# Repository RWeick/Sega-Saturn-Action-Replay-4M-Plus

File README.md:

# Sega-Saturn-Action-Replay-4M-Plus
The Kicad files, rom dump, and PAL JEDEC of the 16V8 for the Sega Saturn Action Replay 4M Plus

PCB Thickness: 1.6 mm

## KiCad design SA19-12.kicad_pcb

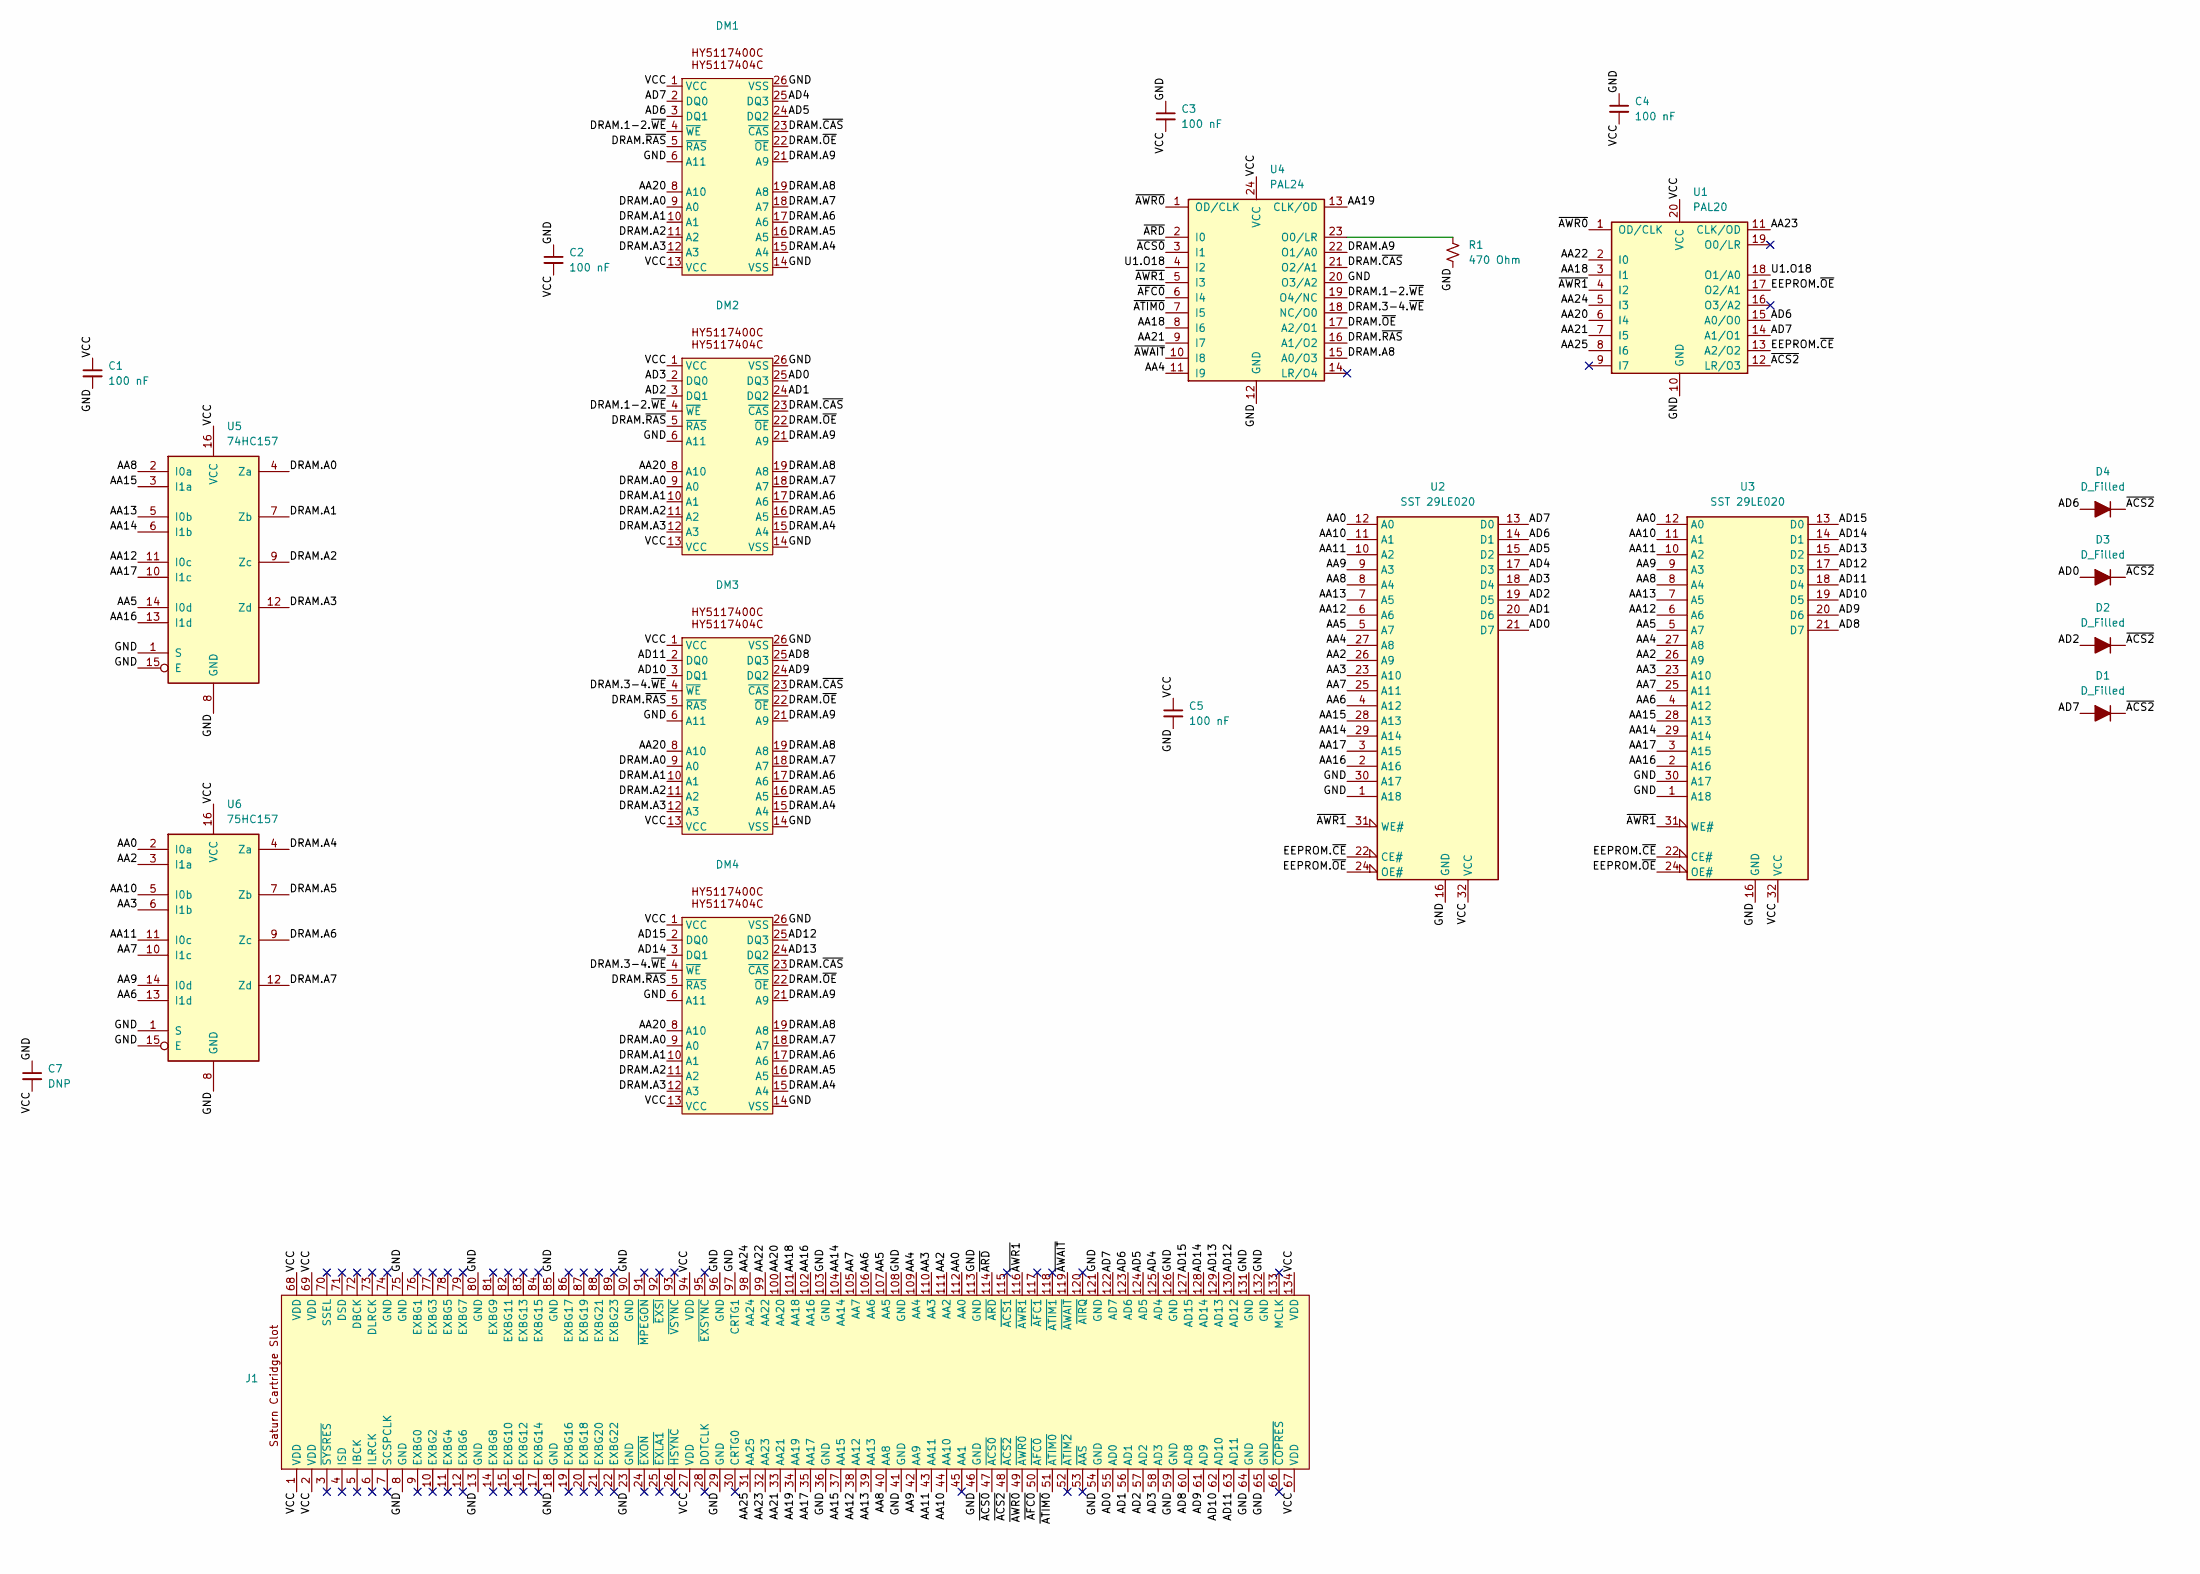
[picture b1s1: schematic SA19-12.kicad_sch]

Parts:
C1, C2, C3, C4, C5: 100 nF; SMD
C7: DNP; SMD
D1, D2, D3, D4: D_Filled; Diode
DM1, DM2, DM3, DM4: DRAM
J1: Edge Connecto5
R1: 470 Ohm; SMD
U1: PAL20; DIP-20_W7.62mm
U2, U3: SST 29LE020; PLCC-32
U4: PAL24; DIP-24_W7.62mm
U5: 74HC157; DIP-16_W7.62mm
U6: 75HC157; DIP-16_W7.62mm

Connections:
/AA0: J1.112 (AA0), U2.12 (A0), U3.12 (A0), U6.2 (I0a)
/AA2: J1.111 (AA2), U2.26 (A9), U3.26 (A9), U6.3 (I1a)
/AA3: J1.110 (AA3), U2.23 (A10), U3.23 (A10), U6.6 (I1b)
/AA4: J1.109 (AA4), U2.27 (A8), U3.27 (A8), U4.11 (I9)
/AA5: J1.107 (AA5), U2.5 (A7), U3.5 (A7), U5.14 (I0d)
/AA6: J1.106 (AA6), U2.4 (A12), U3.4 (A12), U6.13 (I1d)
/AA7: J1.105 (AA7), U2.25 (A11), U3.25 (A11), U6.10 (I1c)
/AA8: J1.40 (AA8), U2.8 (A4), U3.8 (A4), U5.2 (I0a)
/AA9: J1.42 (AA9), U2.9 (A3), U3.9 (A3), U6.14 (I0d)
/AA10: J1.44 (AA10), U2.11 (A1), U3.11 (A1), U6.5 (I0b)
/AA11: J1.43 (AA11), U2.10 (A2), U3.10 (A2), U6.11 (I0c)
/AA12: J1.38 (AA12), U2.6 (A6), U3.6 (A6), U5.11 (I0c)
/AA13: J1.39 (AA13), U2.7 (A5), U3.7 (A5), U5.5 (I0b)
/AA14: J1.104 (AA14), U2.29 (A14), U3.29 (A14), U5.6 (I1b)
/AA15: J1.37 (AA15), U2.28 (A13), U3.28 (A13), U5.3 (I1a)
/AA16: J1.102 (AA16), U2.2 (A16), U3.2 (A16), U5.13 (I1d)
/AA17: J1.35 (AA17), U2.3 (A15), U3.3 (A15), U5.10 (I1c)
/AA18: J1.101 (AA18), U1.3 (I1), U4.8 (I6)
/AA19: J1.34 (AA19), U4.13 (CLK/OD)
/AA20: DM1.8 (A10), DM2.8 (A10), DM3.8 (A10), DM4.8 (A10), J1.100 (AA20), U1.6 (I4)
/AA21: J1.33 (AA21), U1.7 (I5), U4.9 (I7)
/AA22: J1.99 (AA22), U1.2 (I0)
/AA23: J1.32 (AA23), U1.11 (CLK/OD)
/AA24: J1.98 (AA24), U1.5 (I3)
/AA25: J1.31 (AA25), U1.8 (I6)
/AD0: D3.2 (A), DM2.25 (DQ3), J1.55 (AD0), U2.21 (D7)
/AD1: DM2.24 (DQ2), J1.56 (AD1), U2.20 (D6)
/AD2: D2.2 (A), DM2.3 (DQ1), J1.57 (AD2), U2.19 (D5)
/AD3: DM2.2 (DQ0), J1.58 (AD3), U2.18 (D4)
/AD4: DM1.25 (DQ3), J1.125 (AD4), U2.17 (D3)
/AD5: DM1.24 (DQ2), J1.124 (AD5), U2.15 (D2)
/AD6: D4.2 (A), DM1.3 (DQ1), J1.123 (AD6), U1.15 (A0/O0), U2.14 (D1)
/AD7: D1.2 (A), DM1.2 (DQ0), J1.122 (AD7), U1.14 (A1/O1), U2.13 (D0)
/AD8: DM3.25 (DQ3), J1.60 (AD8), U3.21 (D7)
/AD9: DM3.24 (DQ2), J1.61 (AD9), U3.20 (D6)
/AD10: DM3.3 (DQ1), J1.62 (AD10), U3.19 (D5)
/AD11: DM3.2 (DQ0), J1.63 (AD11), U3.18 (D4)
/AD12: DM4.25 (DQ3), J1.130 (AD12), U3.17 (D3)
/AD13: DM4.24 (DQ2), J1.129 (AD13), U3.15 (D2)
/AD14: DM4.3 (DQ1), J1.128 (AD14), U3.14 (D1)
/AD15: DM4.2 (DQ0), J1.127 (AD15), U3.13 (D0)
/DRAM.1-2.~WE: DM1.4 (~WE), DM2.4 (~WE), U4.19 (O4/NC)
/DRAM.3-4.~WE: DM3.4 (~WE), DM4.4 (~WE), U4.18 (NC/O0)
/DRAM.A0: DM1.9 (A0), DM2.9 (A0), DM3.9 (A0), DM4.9 (A0), U5.4 (Za)
/DRAM.A1: DM1.10 (A1), DM2.10 (A1), DM3.10 (A1), DM4.10 (A1), U5.7 (Zb)
/DRAM.A2: DM1.11 (A2), DM2.11 (A2), DM3.11 (A2), DM4.11 (A2), U5.9 (Zc)
/DRAM.A3: DM1.12 (A3), DM2.12 (A3), DM3.12 (A3), DM4.12 (A3), U5.12 (Zd)
/DRAM.A4: DM1.15 (A4), DM2.15 (A4), DM3.15 (A4), DM4.15 (A4), U6.4 (Za)
/DRAM.A5: DM1.16 (A5), DM2.16 (A5), DM3.16 (A5), DM4.16 (A5), U6.7 (Zb)
/DRAM.A6: DM1.17 (A6), DM2.17 (A6), DM3.17 (A6), DM4.17 (A6), U6.9 (Zc)
/DRAM.A7: DM1.18 (A7), DM2.18 (A7), DM3.18 (A7), DM4.18 (A7), U6.12 (Zd)
/DRAM.A8: DM1.19 (A8), DM2.19 (A8), DM3.19 (A8), DM4.19 (A8), U4.15 (A0/O3)
/DRAM.A9: DM1.21 (A9), DM2.21 (A9), DM3.21 (A9), DM4.21 (A9), U4.22 (O1/A0)
/DRAM.~CAS: DM1.23 (~CAS), DM2.23 (~CAS), DM3.23 (~CAS), DM4.23 (~CAS), U4.21 (O2/A1)
/DRAM.~OE: DM1.22 (~OE), DM2.22 (~OE), DM3.22 (~OE), DM4.22 (~OE), U4.17 (A2/O1)
/DRAM.~RAS: DM1.5 (~RAS), DM2.5 (~RAS), DM3.5 (~RAS), DM4.5 (~RAS), U4.16 (A1/O2)
/EEPROM.~CE: U1.13 (A2/O2), U2.22 (CE#), U3.22 (CE#)
/EEPROM.~OE: U1.17 (O2/A1), U2.24 (OE#), U3.24 (OE#)
/GND: C1.2, C2.1, C3.1, C4.1, C5.2, C7.1, DM1.6 (A11), DM1.14 (VSS), DM1.26 (VSS), DM2.6 (A11), DM2.14 (VSS), DM2.26 (VSS), DM3.6 (A11), DM3.14 (VSS), DM3.26 (VSS), DM4.6 (A11), DM4.14 (VSS), DM4.26 (VSS), J1.8 (GND), J1.13 (GND), J1.18 (GND), J1.23 (GND), J1.29 (GND), J1.36 (GND), J1.41 (GND), J1.46 (GND), J1.54 (GND), J1.59 (GND), J1.64 (GND), J1.65 (GND), J1.75 (GND), J1.80 (GND), J1.85 (GND), J1.90 (GND), J1.96 (GND), J1.97 (CRTG1), J1.103 (GND), J1.108 (GND), J1.113 (GND), J1.121 (GND), J1.126 (GND), J1.131 (GND), J1.132 (GND), R1.2, U1.10 (GND), U2.1 (A18), U2.16 (GND), U2.30 (A17), U3.1 (A18), U3.16 (GND), U3.30 (A17), U4.12 (GND), U4.20 (O3/A2), U5.1 (S), U5.8 (GND), U5.15 (E), U6.1 (S), U6.8 (GND), U6.15 (E)
/U1.O18: U1.18 (O1/A0), U4.4 (I2)
/VCC: C1.1, C2.2, C3.2, C4.2, C5.1, C7.2, DM1.1 (VCC), DM1.13 (VCC), DM2.1 (VCC), DM2.13 (VCC), DM3.1 (VCC), DM3.13 (VCC), DM4.1 (VCC), DM4.13 (VCC), J1.1 (VDD), J1.2 (VDD), J1.27 (VDD), J1.67 (VDD), J1.68 (VDD), J1.69 (VDD), J1.94 (VDD), J1.134 (VDD), U1.20 (VCC), U2.32 (VCC), U3.32 (VCC), U4.24 (VCC), U5.16 (VCC), U6.16 (VCC)
/~ACS0: J1.47 (~ACS0), U4.3 (I1)
/~ACS2: D1.1 (K), D2.1 (K), D3.1 (K), D4.1 (K), J1.48 (~ACS2), U1.12 (LR/O3)
/~AFC0: J1.50 (~AFC0), U4.6 (I4)
/~ARD: J1.114 (~ARD), U4.2 (I0)
/~ATIM0: J1.51 (~ATIM0), U4.7 (I5)
/~AWAIT: J1.119 (~AWAIT), U4.10 (I8)
/~AWR0: J1.49 (~AWR0), U1.1 (OD/CLK), U4.1 (OD/CLK)
/~AWR1: J1.116 (~AWR1), U1.4 (I2), U2.31 (WE#), U3.31 (WE#), U4.5 (I3)
unnamed: R1.1, U4.23 (O0/LR)

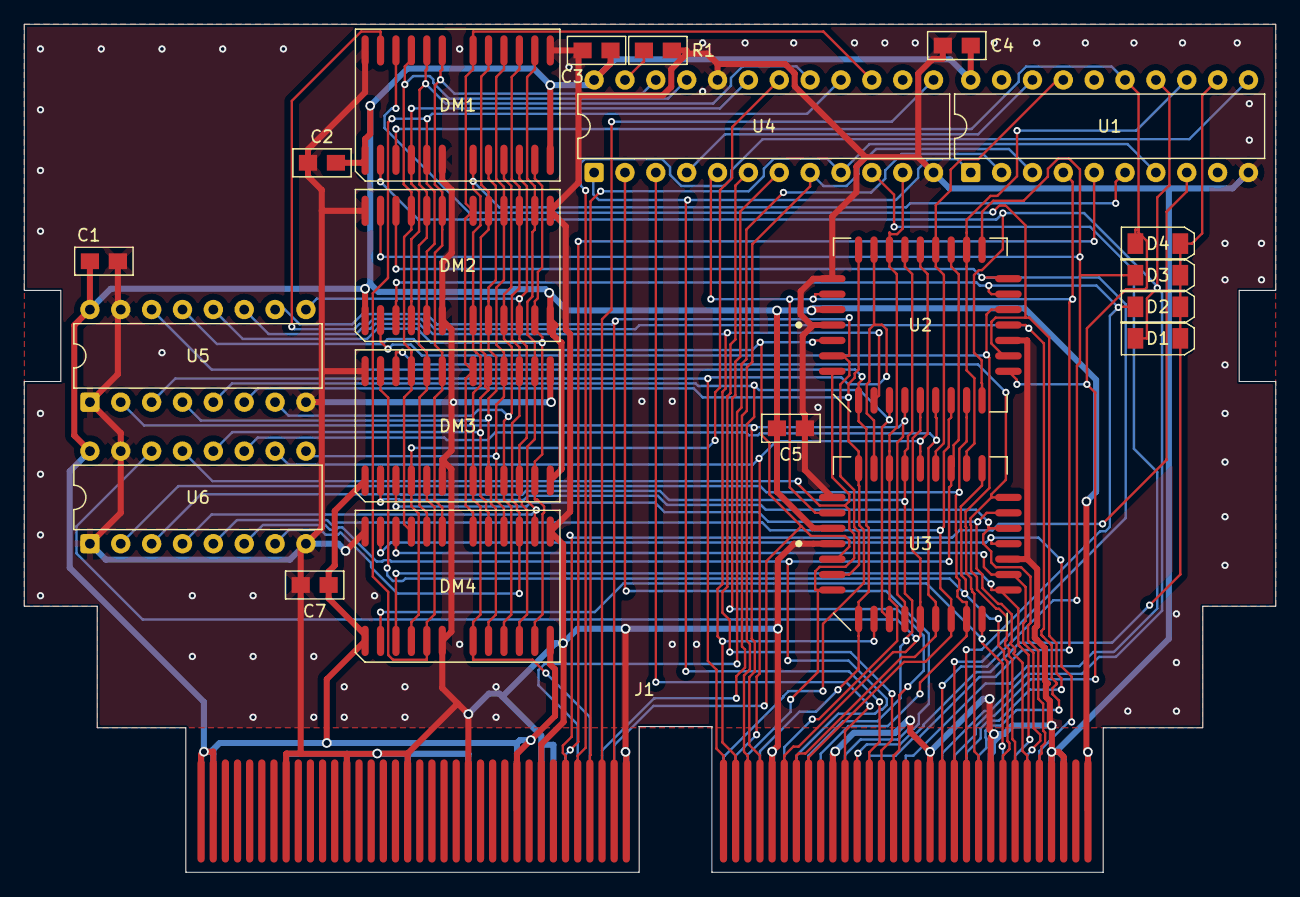
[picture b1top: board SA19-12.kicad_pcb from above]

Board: 2 copper layers, 103.0 x 69.8 mm, 22 parts (0 on the bottom side), 70 nets.
